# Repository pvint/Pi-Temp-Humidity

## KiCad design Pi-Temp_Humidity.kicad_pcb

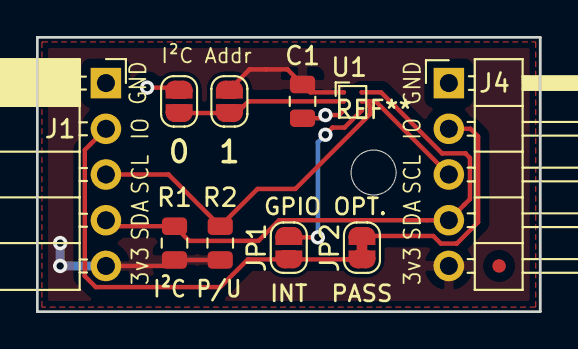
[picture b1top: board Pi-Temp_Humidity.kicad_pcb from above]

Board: 2 copper layers, 27.9 x 15.2 mm, 10 parts (0 on the bottom side), 8 nets.

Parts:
C1: 0.1uF; C_0805_2012Metric
J1: Conn_01x05; PinSocket_1x05_P2.54mm_Horizontal
J4: Conn_01x05; PinHeader_1x05_P2.54mm_Horizontal
JP1, JP3, JP4: SolderJumper_2_Open; SolderJumper-2_P1.3mm_Open_RoundedPad1.0x1.5mm
JP2: SolderJumper_2_Bridged; SolderJumper-2_P1.3mm_Bridged_RoundedPad1.0x1.5mm
R1, R2: 10k; R_0805_2012Metric
U1: HDC2010; Texas_DSBGA-6

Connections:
Earth: C1.2, J1.1, J4.1, JP4.2, U1.C1
GPIO: J1.2, JP1.1, JP2.1
GPIO_PASSTHRU: J4.2, JP2.2
unnamed: JP1.2, U1.C2
unnamed: JP3.2, JP4.1, U1.B1
SCL: J1.3, J4.3, R2.2, U1.B2
SDA: J1.4, J4.4, R1.2, U1.A2
VDD: C1.1, J1.5, J4.5, JP3.1, R1.1, R2.1, U1.A1

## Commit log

2018-11-11 Initial Import
2018-11-11 Tidy up and create gerbers
2019-02-10 Fixed footprint on HDC2010 & panelized
